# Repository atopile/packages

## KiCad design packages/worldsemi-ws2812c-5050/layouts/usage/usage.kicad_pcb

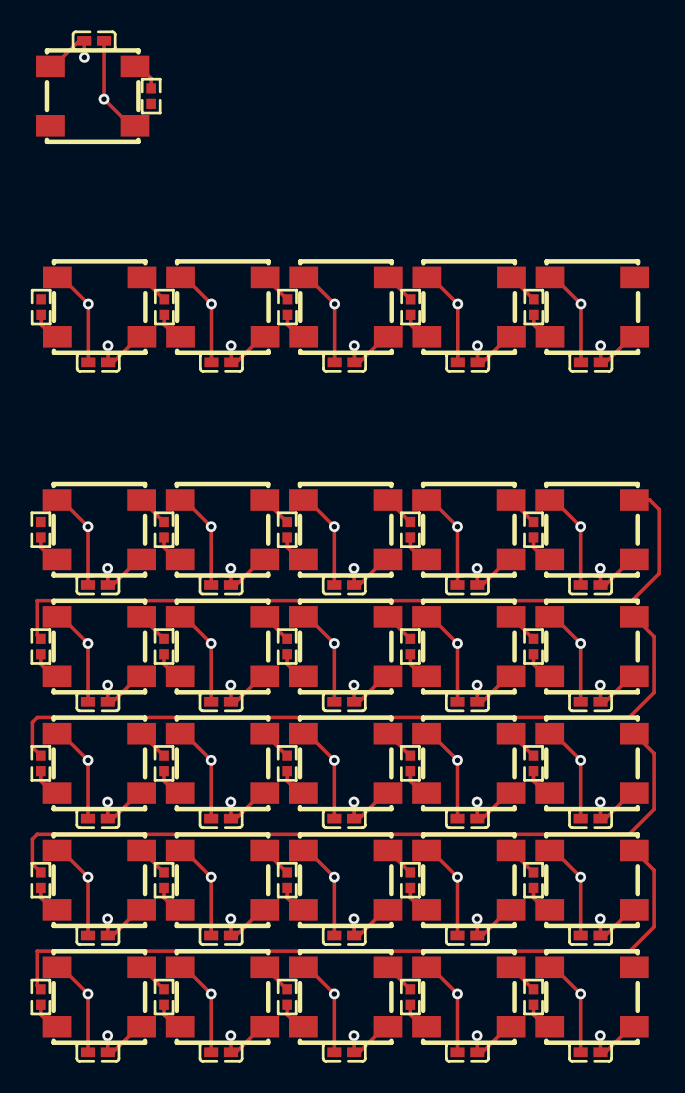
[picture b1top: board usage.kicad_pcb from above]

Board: 2 copper layers, 93 parts (0 on the bottom side), 61 nets.

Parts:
C1, C2, C3, C4, C5, C6, C7, C8, C9, C10, C11, C12, C13, C14, C15, C16, C17, C18, C19, C20, C21, C22, C23, C24, C25, C26, C27, C28, C29, C30, C31: 100nF ±10% 16V X7R; C0402
LED1, LED2, LED3, LED4, LED5, LED6, LED7, LED8, LED9, LED10, LED11, LED12, LED13, LED14, LED15, LED16, LED17, LED18, LED19, LED20, LED21, LED22, LED23, LED24, LED25, LED26, LED27, LED28, LED29, LED30, LED31: LED-SMD_4P-L5.0-W5.0-LS5.4-TL-1
R1, R2, R3, R4, R5, R6, R7, R8, R9, R10, R11, R12, R13, R14, R15, R16, R17, R18, R19, R20, R21, R22, R23, R24, R25, R26, R27, R28, R29, R30, R31: 330Ω ±1% 62.5mW; R0402

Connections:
GND: C1.2, C2.2, C3.2, C4.2, C5.2, C6.2, C7.2, C8.2, C9.2, C10.2, C11.2, C12.2, C13.2, C14.2, C15.2, C16.2, C17.2, C18.2, C19.2, C20.2, C21.2, C22.2, C23.2, C24.2, C25.2, C26.2, C27.2, C28.2, C29.2, C30.2, C31.2, LED1.3, LED2.3, LED3.3, LED4.3, LED5.3, LED6.3, LED7.3, LED8.3, LED9.3, LED10.3, LED11.3, LED12.3, LED13.3, LED14.3, LED15.3, LED16.3, LED17.3, LED18.3, LED19.3, LED20.3, LED21.3, LED22.3, LED23.3, LED24.3, LED25.3, LED26.3, LED27.3, LED28.3, LED29.3, LED30.3, LED31.3
VCC: C1.1, C2.1, C3.1, C4.1, C5.1, C6.1, C7.1, C8.1, C9.1, C10.1, C11.1, C12.1, C13.1, C14.1, C15.1, C16.1, C17.1, C18.1, C19.1, C20.1, C21.1, C22.1, C23.1, C24.1, C25.1, C26.1, C27.1, C28.1, C29.1, C30.1, C31.1, LED1.1, LED2.1, LED3.1, LED4.1, LED5.1, LED6.1, LED7.1, LED8.1, LED9.1, LED10.1, LED11.1, LED12.1, LED13.1, LED14.1, LED15.1, LED16.1, LED17.1, LED18.1, LED19.1, LED20.1, LED21.1, LED22.1, LED23.1, LED24.1, LED25.1, LED26.1, LED27.1, LED28.1, LED29.1, LED30.1, LED31.1
data_protection_r-DIN-0: LED6.4, R6.2
data_protection_r-DIN-1: LED7.4, R7.2
data_protection_r-DIN-2: LED8.4, R8.2
data_protection_r-DIN-3: LED9.4, R9.2
data_protection_r-DIN-4: LED10.4, R10.2
data_protection_r-DIN-5: LED11.4, R11.2
data_protection_r-DIN-6: LED12.4, R12.2
data_protection_r-DIN-7: LED13.4, R13.2
data_protection_r-DIN-8: LED14.4, R14.2
data_protection_r-DIN-9: LED15.4, R15.2
data_protection_r-DIN-10: LED17.4, R17.2
data_protection_r-DIN-11: LED18.4, R18.2
data_protection_r-DIN-12: LED19.4, R19.2
data_protection_r-DIN-13: LED20.4, R20.2
data_protection_r-DIN-14: LED21.4, R21.2
data_protection_r-DIN-15: LED22.4, R22.2
data_protection_r-DIN-16: LED23.4, R23.2
data_protection_r-DIN-17: LED24.4, R24.2
data_protection_r-DIN-18: LED25.4, R25.2
data_protection_r-DIN-19: LED26.4, R26.2
data_protection_r-DIN-20: LED27.4, R27.2
data_protection_r-DIN-21: LED28.4, R28.2
data_protection_r-DIN-22: LED29.4, R29.2
data_protection_r-DIN-23: LED30.4, R30.2
data_protection_r-DIN-24: LED31.4, R31.2
data_protection_r-DIN-25: LED1.4, R1.2
data_protection_r-DIN-26: LED2.4, R2.2
data_protection_r-DIN-27: LED3.4, R3.2
data_protection_r-DIN-28: LED4.4, R4.2
data_protection_r-DIN-29: LED5.4, R5.2
data_protection_r-DIN-30: LED16.4, R16.2
leds[1]-data_in-DOUT-0: LED6.2, R7.1
leds[1]-data_in-DOUT-1: LED11.2, R12.1
leds[1]-data_in-DOUT-2: LED17.2, R18.1
leds[1]-data_in-DOUT-3: LED22.2, R23.1
leds[1]-data_in-DOUT-4: LED27.2, R28.1
leds[1]-data_in-DOUT-5: LED1.2, R2.1
leds[2]-data_in-DOUT-0: LED7.2, R8.1
leds[2]-data_in-DOUT-1: LED12.2, R13.1
leds[2]-data_in-DOUT-2: LED18.2, R19.1
leds[2]-data_in-DOUT-3: LED23.2, R24.1
leds[2]-data_in-DOUT-4: LED28.2, R29.1
leds[2]-data_in-DOUT-5: LED2.2, R3.1
leds[3]-data_in-DOUT-0: LED8.2, R9.1
leds[3]-data_in-DOUT-1: LED13.2, R14.1
leds[3]-data_in-DOUT-2: LED19.2, R20.1
leds[3]-data_in-DOUT-3: LED24.2, R25.1
leds[3]-data_in-DOUT-4: LED29.2, R30.1
leds[3]-data_in-DOUT-5: LED3.2, R4.1
leds[4]-data_in-DOUT-0: LED9.2, R10.1
leds[4]-data_in-DOUT-1: LED14.2, R15.1
leds[4]-data_in-DOUT-2: LED20.2, R21.1
leds[4]-data_in-DOUT-3: LED25.2, R26.1
leds[4]-data_in-DOUT-4: LED30.2, R31.1
leds[4]-data_in-DOUT-5: LED4.2, R5.1
strips[1]-data_in-line: LED10.2, R11.1
strips[2]-data_in-line: LED15.2, R17.1
strips[3]-data_in-line: LED21.2, R22.1
strips[4]-data_in-line: LED26.2, R27.1

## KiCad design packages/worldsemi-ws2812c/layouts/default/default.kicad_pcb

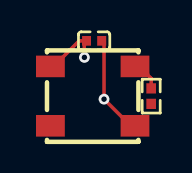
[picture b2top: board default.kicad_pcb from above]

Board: 2 copper layers, 3 parts (0 on the bottom side), 3 nets.

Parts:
C1: 1.0000000000000001e-07F; C0402
LED1: LED-SMD_4P-L5.0-W5.0-LS5.4-TL-1
R1: 330.0Ω; R0402

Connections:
DIN: LED1.4, R1.2
hv: C1.1, LED1.1
lv: C1.2, LED1.3

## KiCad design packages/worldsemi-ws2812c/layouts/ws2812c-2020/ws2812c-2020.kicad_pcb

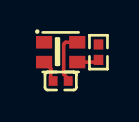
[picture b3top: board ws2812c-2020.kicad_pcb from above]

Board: 2 copper layers, 3 parts (0 on the bottom side), 3 nets.

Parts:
C1: 100nF ±10%; C0402
LED1: LED-SMD_4P-L2.0-W2.0-TL_WS2812B-2020
R1: 330Ω ±1%; R0402

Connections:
DI: LED1.3, R1.2
hv: C1.1, LED1.4
lv: C1.2, LED1.2

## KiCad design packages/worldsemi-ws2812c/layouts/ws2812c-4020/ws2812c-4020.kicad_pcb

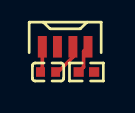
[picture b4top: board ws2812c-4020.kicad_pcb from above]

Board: 2 copper layers, 3 parts (0 on the bottom side), 3 nets.

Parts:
C1: 100nF ±10%; C0402
LED1: LED-SMD_4P-L4.0-W1.7-R
R1: 330Ω ±1%; R0402

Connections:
DIN: LED1.1, R1.2
hv: C1.1, LED1.2
lv: C1.2, LED1.4
